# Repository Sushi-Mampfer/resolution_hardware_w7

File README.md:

# HugeTiny1616
A pretty big devboard for the ATTINY1616, with 4 buttons and a screen, perfect to play pong with a friend.

## [KiCanvas](https://kicanvas.org/?repo=https%3A%2F%2Fgithub.com%2FSushi-Mampfer%2Fresolution_hardware_w7%2Ftree%2F%2Fsrc%2Fkicad)

## Schematic

## PCB

## 3D (Don't ask me why nothing is 3d, I've added it and it shows in the preview)

## Case

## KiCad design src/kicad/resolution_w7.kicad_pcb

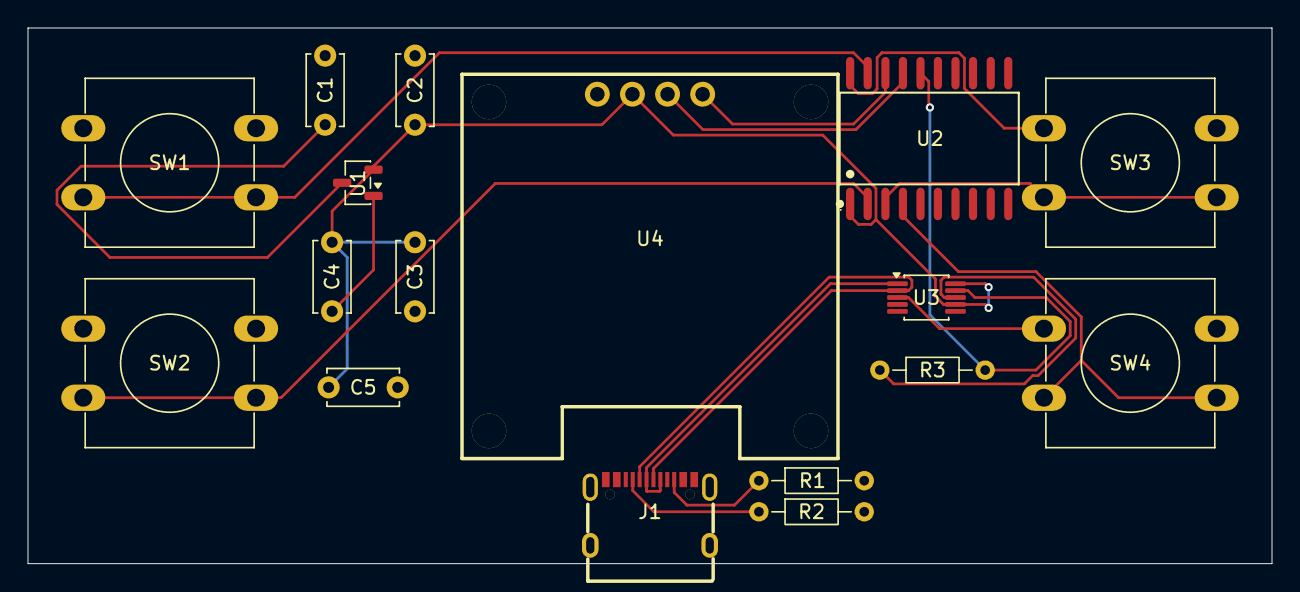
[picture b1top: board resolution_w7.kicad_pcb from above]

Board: 2 copper layers, 90.0 x 38.8 mm, 17 parts (0 on the bottom side), 15 nets.

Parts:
C1, C2, C4: 1uF; C_Disc_D5.0mm_W2.5mm_P5.00mm
C3: 100nF; C_Disc_D5.0mm_W2.5mm_P5.00mm
C5: 0.1uF; C_Disc_D5.0mm_W2.5mm_P5.00mm
J1: USB_C_Receptacle_USB2.0_16P; USB-C-SMD_TYPE-C-16PIN-2MD-073
R1, R2: 5.1k; R_Axial_DIN0204_L3.6mm_D1.6mm_P7.62mm_Horizontal
R3: 1k; R_Axial_DIN0204_L3.6mm_D1.6mm_P7.62mm_Horizontal
SW1, SW2, SW3, SW4: SW_Push; SW_PUSH-12mm
U1: XC6206PxxxMR; SOT-23-3
U2: ATtiny1616-S; SOIC-20_L13.0-W7.6-P1.27-LS10.3-BL
U3: CH340X; MSOP-10_3x3mm_P0.5mm
U4: HS96L03W2C03; OLED-TH_L27.8-W27.2-P2.54_C9900033791

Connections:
+3.3V: C2.1, C3.1, C4.1, C5.1, U1.2 (VO), U2.1 (VCC), U3.7 (VCC), U3.10 (V3), U4.2 (VCC)
/SCL: U2.17 (PA1), U4.3 (SCL)
/SDA: U2.18 (PA2), U4.4 (SDA)
/UPDI: R3.2, U2.16 (~RESET/PA0), U3.9 (RXD)
/USB_D+: J1.A6 (D+), J1.B6 (D+), U3.1 (UD+)
/USB_D-: J1.A7 (D-), J1.B7 (D-), U3.2 (UD-)
/p1_down: SW2.2, U2.2 (PA4)
/p1_up: SW1.2, U2.19 (PA3)
/p2_down: SW4.2, U2.4 (PA6)
/p2_up: SW3.2, U2.3 (PA5)
GND: C1.2, C2.2, C3.2, C4.2, C5.2, R1.2, R2.2, SW1.1, SW2.1, SW3.1, SW4.1, U1.1 (GND), U2.20 (GND), U3.3 (GND), U4.1 (GND)
unnamed: J1.A5 (CC1), R2.1
unnamed: J1.B5 (CC2), R1.1
unnamed: R3.1, U3.8 (TXD)
VBUS: C1.1, U1.3 (VI)

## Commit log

2026-05-26 Add Case section with an image to README
